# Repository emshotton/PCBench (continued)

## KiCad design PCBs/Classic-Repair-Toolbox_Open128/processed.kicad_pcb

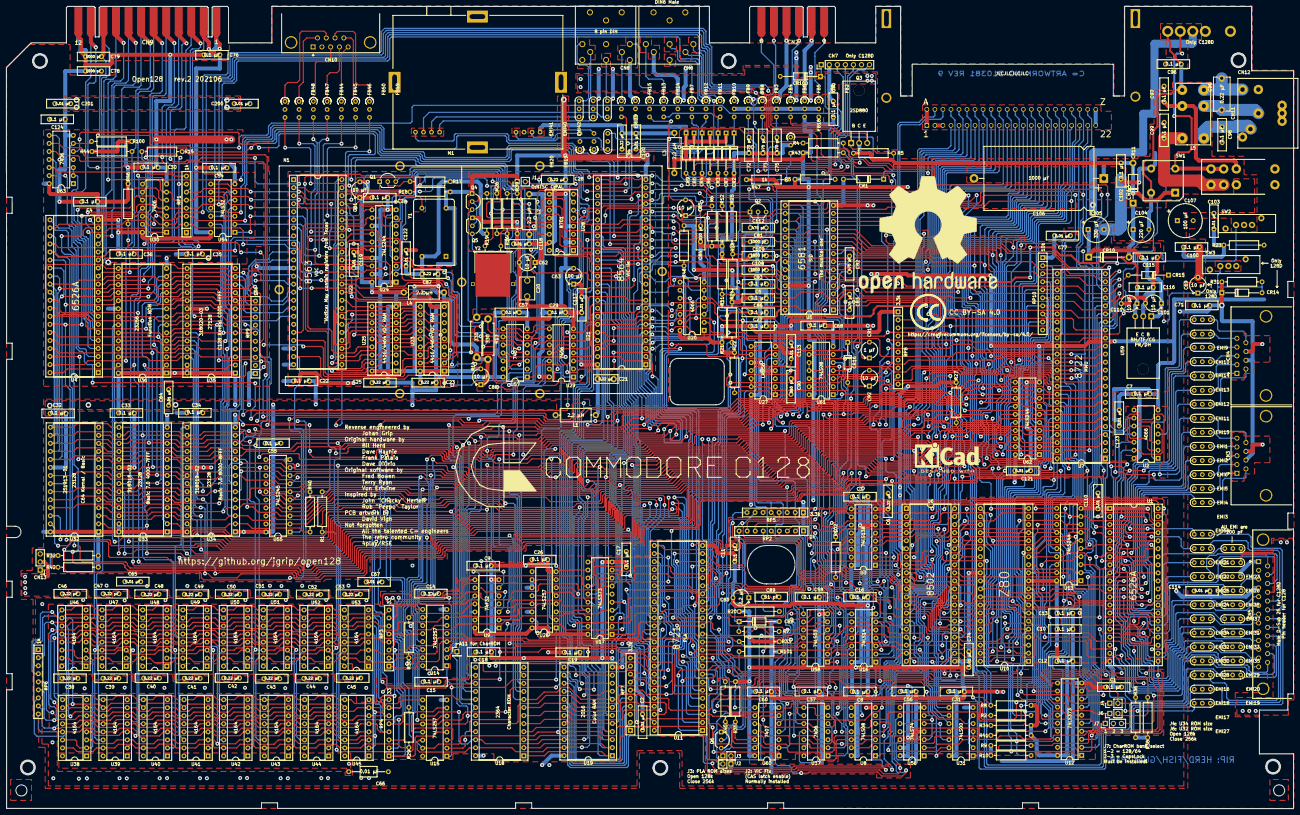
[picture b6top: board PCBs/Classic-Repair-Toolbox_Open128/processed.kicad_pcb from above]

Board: 2 copper layers, 406.6 x 253.4 mm, 371 parts (1 on the bottom side), 400 nets.

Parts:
C1, C3, C4, C5, C7, C8, C9, C10, C11, C12, C13, C14, C15, C16, C17, C18, C19, C22, C24, C26, C27, C29, C30, C31, C32, C33, C34, C35, C36, C37, C54, C55, C56, C57, C58, C60, C68, C70, C71, C76, C86, C93, C96, C97, C98, C99, C100, C102, C115, C116, C124: 0.1 µF; C_Disc_D10.0mm_W2.5mm_P5.00mm
C2, C64, C65, C67, C74, C77, C103, C110, C113, C114, C117, C118, C119, C120, C121, C122, C123, C200, C201: 0.01 µF; C_Disc_D10.0mm_W2.5mm_P5.00mm
C6, C23, C25, C28, C38, C39, C40, C41, C42, C43, C44, C45, C46, C47, C48, C49, C50, C51, C52, C53, C87, C94: 0.22 µF; C_Disc_D10.0mm_W2.5mm_P5.00mm
C20: 40 pF; C_Adjustable_L7.0mm_W4.5mm_P5.00mm
C21: 0.22 µF; C_Disc_D7.5mm_W2.5mm_P5.00mm
C61, C62, C69, C85, C88, C92, C101, C111: 10 µF; CP_Radial_Tantal_D5.0mm_P5.00mm
C63: 100 µF; CP_Radial_Tantal_D5.0mm_P5.00mm
C66: 0.01 µF; C_Axial_L5.1mm_D3.1mm_P12.50mm_Horizontal
C72, C73, C75, C82, C83, C112: 470 pF; C_Disc_D10.0mm_W2.5mm_P5.00mm
C78, C79, C81: 1000 pF; C_Disc_D10.0mm_W2.5mm_P5.00mm
C80: 2.2 µF; CP_Radial_Tantal_D5.0mm_P5.00mm
C84: 220 pF; C_Disc_D10.0mm_W2.5mm_P5.00mm
C89: 51 pF; C_Disc_D10.0mm_W2.5mm_P5.00mm
C90: 360 pF; C_Disc_D10.0mm_W2.5mm_P5.00mm
C91: 1 µF; CP_Radial_Tantal_D5.0mm_P5.00mm
C95: 0.22 µF; C_Disc_D10.5mm_W5.0mm_P10.00mm
C104: 220 µF; CP_Radial_Tantal_D8.0mm_P5.00mm
C105: 330 µF; CP_Radial_Tantal_D8.0mm_P5.00mm
C106: 1000 µF; CP_Axial_L34.5mm_D20.0mm_P41.00mm_Horizontal
C107: 100 µF; CP_Radial_Tantal_D10.5mm_P5.00mm
C108, C109: 1800 pF; C_Disc_D10.0mm_W2.5mm_P5.00mm
CN1: Expansion bus; EXPANSIONPORT
CN2: Cassette; CASSETTEPORT
CN3: Port1 Male DB9; DSUB-9_Male_Horizontal_P2.77x2.84mm_EdgePinOffset14.56mm_Ho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
CN4: Port2 Male DB9; DSUB-9_Male_Horizontal_P2.77x2.84mm_EdgePinOffset14.56mm_Ho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
CN5: Conn_01x25; DSUB-25_Female_Horizontal_P2.77x2.84mm_EdgePinOffset7.70mm_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
CN6: DIN6 Male; Connector_DIN_Female_6Pin_3rows
CN7: 7 pin post; PinHeader_1x07_P2.54mm_Vertical
CN8: 8 pin DIN; Connector_DIN_Female_8Pin_3rows
CN9: User Port; USERPORT
CN10: RGBI 9-pin DIN; DSUB-9_Male_Horizontal_P2.77x2.84mm_EdgePinOffset7.70mm_Hou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
CN11: Power DIN connector; Connector_Power_5pin_252167_01
CN12: 6 pin post; CN12_C128D_power
CN13: Power LED; PinHeader_1x03_P2.54mm_Vertical
CN20: TA11; PinHeader_1x01_P2.54mm_Vertical
CR1: 6.8v; D_DO-35_SOD27_P12.70mm_Horizontal
CR2, CR3, CR4, CR5, CR6, CR7, CR9, CR14, CR15, CR16, CR100: 1N914; D_DO-35_SOD27_P12.70mm_Horizontal
CR8: 1N4371; D_DO-35_SOD27_P12.70mm_Horizontal
CR10, CR11: 1N4001; D_DO-41_SOD81_P12.70mm_Horizontal
CR13: 251026-01; BRIDGE_RECTIFIER
EMI1, EMI2, EMI9, EMI10, EMI11: 47 pF; EMI-Filter
EMI3, EMI4, EMI5, EMI6, EMI12, EMI13, EMI14, EMI15, EMI16, EMI17, EMI18, EMI19, EMI20, EMI21, EMI22, EMI23, EMI24, EMI25, EMI26, EMI27, EMI28, EMI29, EMI30, EMI31, EMI32, EMI33, EMI34, EMI35, EMI37, EMI38, EMI40, EMI41, EMI42, EMI69: 100 pF; EMI-Filter
EMI39: 270 pF; EMI-Filter
FB1, FB2, FB3, FB4, FB5, FB6, FB7, FB8, FB9, FB10, FB11, FB12, FB13, FB14, FB15, FB18, FB19, FB20, FB44, FB45, FB46, FB47, FB48, FB49, FB50: Ferrite_Bead_Small; Ferrite_Bead_vertical
J1: C:PAL / O:NTSC; PinHeader_1x02_P2.54mm_Vertical
J2, J3: Close to enable CAS latch; PinHeader_1x02_P2.54mm_Vertical
J4, J6: 128/256k; PinHeader_1x02_P2.54mm_Vertical
J7: SolderJumper_3_Bridged12; PinHeader_1x03_P2.54mm_Vertical
L1, L2, L3, L4: 2.2 µH; L_Axial_L9.5mm_D4.0mm_P12.70mm_Horizontal_Fastron_SMCC
L5: 251878-01; Noise_Filter_Power_251878_01
LOGO1: OSHW logo; OSHW-Logo2_48.7x40mm_SilkScreen
LOGO2: KiCad logo; KiCad-Logo2_8mm_SilkScreen
LOGO3: C128 logo; C128-logo
LOGO4: Creative Commons; Symbol_CreativeCommons_SilkScreenTop_Type2_Big
M1: RF_Modulator; RF_modulator
N1: RF Cage; RF_Cage
Q1, Q2, Q4, Q5, Q6: 2SC1815; TO-92_Inline_Wide
Q3: 2SD880; TO-220-3_Horizontal_TabDown
R1, R29, R30, R40, R102: 68; R_Axial_DIN0309_L9.0mm_D2.5mm_P12.70mm_Horizontal
R2, R4, R15, R26, R35: 100; R_Axial_DIN0309_L9.0mm_D2.5mm_P12.70mm_Horizontal
R3, R11, R12, R47, R100, R101: 1k; R_Axial_DIN0309_L9.0mm_D2.5mm_P12.70mm_Horizontal
R5: 470; R_Axial_DIN0309_L9.0mm_D2.5mm_P12.70mm_Horizontal
R6, R22, R24: 47k; R_Axial_DIN0309_L9.0mm_D2.5mm_P12.70mm_Horizontal
R7: 560; R_Axial_DIN0309_L9.0mm_D2.5mm_P12.70mm_Horizontal
R8, R10, R43, R44, R46: 3.3k; R_Axial_DIN0309_L9.0mm_D2.5mm_P12.70mm_Horizontal
R9, R20, R28, R33, R34, R36, R38, R48: 10k; R_Axial_DIN0309_L9.0mm_D2.5mm_P12.70mm_Horizontal
R13, R14: 330; R_Axial_DIN0411_L9.9mm_D3.6mm_P12.70mm_Horizontal
R16, R39: 120; R_Axial_DIN0309_L9.0mm_D2.5mm_P12.70mm_Horizontal
R17: 47; R_Axial_DIN0309_L9.0mm_D2.5mm_P12.70mm_Horizontal
R18: 82; R_Axial_DIN0309_L9.0mm_D2.5mm_P12.70mm_Horizontal
R19: 330; R_Axial_DIN0309_L9.0mm_D2.5mm_P12.70mm_Horizontal
R21: 470k; R_Axial_DIN0309_L9.0mm_D2.5mm_P12.70mm_Horizontal
R23, R25, R31: 100k; R_Axial_DIN0309_L9.0mm_D2.5mm_P12.70mm_Horizontal
R27: 4.7k; R_Axial_DIN0309_L9.0mm_D2.5mm_P12.70mm_Horizontal
R32, R42: 180; R_Axial_DIN0309_L9.0mm_D2.5mm_P12.70mm_Horizontal
R41: 680; R_Axial_DIN0309_L9.0mm_D2.5mm_P12.70mm_Horizontal
R45: 1.2k; R_Axial_DIN0309_L9.0mm_D2.5mm_P12.70mm_Horizontal
RP1: 1k; R_Array_SIP8
RP2, RP6: 1k; R_Array_SIP9
RP3, RP4: 33; R_Array_SIP8
RP5: 3.3k; R_Array_SIP8
RP7, RP8: 3.3k; R_Array_SIP10
RP9, RP10: 10k; R_Array_SIP10
SW1: Power switch; Power_Switch
SW2: Reset Switch; Switch-Pushbutton
SW3: Disk Reset; Switch-Pushbutton
U1, U4: 6526A; DIP-40_W15.24mm_Socket
U2, U20: 4066; DIP-14_W7.62mm
U3: 74LS138; DIP-16_W7.62mm
U5: 6581; DIP-28_W15.24mm_Socket
U6: 8502; DIP-40_W15.24mm_Socket
U7: 8722; DIP-48_W15.24mm_Socket
U8, U61: 74LS08; DIP-14_W7.62mm
U9: 74F32; DIP-14_W7.62mm
U10: Z80; DIP-40_W15.24mm_Socket
U11: 8721; DIP-48_W15.24mm_Socket
U12, U17: 74LS373; DIP-20_W7.62mm
U13, U24, U62: 74LS244; DIP-20_W7.62mm
U14, U15, U26: 74LS257; DIP-16_W7.62mm
U16: 74LS14; DIP-14_W7.62mm
U18: 2364; DIP-24_W15.24mm_Socket
U19: 2016; DIP-24_W15.24mm_Socket
U21: 8564; DIP-48_W15.24mm_Socket
U22: 8563; DIP-48_W15.24mm_Socket
U23, U25: 4464; DIP-18_W7.62mm_Socket
U27: LM556; DIP-14_W7.62mm
U28: 8701; DIP-16_W7.62mm_Socket
U29, U30, U37, U63: 7406; DIP-14_W7.62mm
U31: 74LS00; DIP-14_W7.62mm
U32, U33, U34: 23128; DIP-28_W15.24mm_Socket
U35: 318020-03; DIP-28_W15.24mm_Socket
U36: 23256; DIP-28_W15.24mm_Socket
U38, U39, U40, U41, U42, U43, U44, U45, U46, U47, U48, U49, U50, U51, U52, U53: 4164; DIP-16_W7.62mm_Socket
U54: 74LS32; DIP-14_W7.62mm
U55: 74LS245; DIP-20_W7.62mm
U56: 74LS74; DIP-14_W7.62mm
U57, U60: 7407; DIP-14_W7.62mm
U58: 74LS03; DIP-14_W7.62mm
U59: L7812; TO-220-3_Horizontal_TabDown
Y1: 16 MHz; Oscillator_DIP-14
Y2: 17.73447 MHz (PAL) / 14.31818 MHz (NTSC); Crystal_HC49-U_Horizontal_1EP_style2

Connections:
1MHZ: CN1.E, R102.2, U4.25, U5.6, U21.18
2MHZ: U6.1, U7.33, U21.23, U22.4
9VAC1: C79.2, CN9.10, CN12.5, CR13.2, R7.1, SW1.4
9VAC2: C78.2, C96.1, C104.2, CN9.11, CN12.6, CR13.4, L5.6
40_80: EMI16.3, RP8.9, U7.48
128_64: J6.1, J7.1, U7.47, U8.9, U11.15
+5V: C1.2, C2.1, C3.2, C4.2, C5.2, C6.2, C7.1, C8.2, C9.2, C10.2, C11.2, C12.2, C13.2, C14.2, C15.2, C16.2, C17.2, C18.2, C19.2, C22.2, C23.2, C24.2, C25.2, C26.2, C27.1, C29.2, C30.2, C31.2, C32.2, C33.2, C34.2, C35.2, C36.2, C37.2, C38.1, C39.1, C40.1, C41.1, C42.1, C43.1, C44.1, C45.1, C46.1, C47.1, C48.1, C49.1, C50.1, C51.1, C52.1, C53.1, C54.2, C55.2, C56.2, C57.2, C58.2, C60.2, C61.1, C64.1, C65.1, C66.1, C67.1, C68.2, C70.2, C71.1, C74.2, C76.2, C77.2, C100.1, C103.1, C107.1, C110.2, C114.1, C119.2, C121.2, C123.2, C124.2, CN1.2, CN1.3, CN3.7, CN4.7, CN5.4, CN9.2, CN12.4, CR5.1, CR6.1, CR7.1, CR9.1, CR14.1, CR15.1, FB1.2, FB13.2, L1.2, L2.1, L3.1, L4.1, R3.1, R8.2, R9.1, R10.1, R20.1, R21.1, R22.1, R23.1, R24.1, R27.1, R31.1, R32.2, R33.1, R34.2, R35.2, R36.2, R38.1, R40.1, R41.2, R42.2, R43.1, R44.1, R46.1, R47.1, R48.2, R100.1, RP1.1, RP2.1, RP5.1, RP6.1, RP7.1, RP8.1, RP9.1, RP10.1, SW1.2, U1.20, U2.14, U3.6, U3.16, U4.20, U5.25, U6.6, U7.1, U8.14, U9.14, U10.11, U11.8, U11.48, U12.20, U13.20, U14.16, U15.16, U16.14, U17.20, U18.24, U19.24, U20.14, U22.37, U23.9, U24.20, U25.9, U26.16, U27.4, U27.10, U27.14, U29.14, U30.14, U31.14, U32.1, U32.28, U33.1, U33.27, U33.28, U34.1, U34.28, U35.1, U35.27, U35.28, U36.1, U36.28, U37.14, U38.8, U39.8, U40.8, U41.8, U42.8, U43.8, U44.8, U45.8, U46.8, U47.8, U48.8, U49.8, U50.8, U51.8, U52.8, U53.8, U54.14, U55.20, U56.1, U56.4, U56.13, U56.14, U57.14, U58.14, U60.14, U61.14, U62.20, U63.14
+9V: C102.1, C106.1, CR11.2, CR13.1, Q3.2, R5.2
+12V: C86.2, C111.1, C116.1, Q2.2, R45.2, U5.28, U59.3
/Address Multiplexing/A0: RP9.10, U1.38, U4.38, U5.9, U6.7, U7.18, U10.30, U15.13, U22.8, U32.10, U33.10, U34.10, U35.10, U36.10, U55.3
/Address Multiplexing/A1: RP9.9, U1.37, U4.37, U5.10, U6.8, U7.19, U10.31, U15.10, U32.9, U33.9, U34.9, U35.9, U36.9, U55.5
/Address Multiplexing/A2: RP9.8, U1.36, U4.36, U5.11, U6.9, U7.20, U10.32, U15.6, U32.8, U33.8, U34.8, U35.8, U36.8, U55.7
/Address Multiplexing/A3: RP9.7, U1.35, U4.35, U5.12, U6.10, U7.21, U10.33, U15.3, U32.7, U33.7, U34.7, U35.7, U36.7, U55.9
/Address Multiplexing/A4: RP9.6, U5.13, U6.11, U10.34, U14.13, U32.6, U33.6, U34.6, U35.6, U36.6, U54.13, U55.8
/Address Multiplexing/A5: RP9.5, U6.12, U10.35, U14.10, U32.5, U33.5, U34.5, U35.5, U36.5, U54.12, U55.6
/Address Multiplexing/A6: RP9.4, U6.13, U10.36, U14.6, U32.4, U33.4, U34.4, U35.4, U36.4, U54.5, U55.4
/Address Multiplexing/A7: RP9.3, U6.14, U10.37, U14.3, U32.3, U33.3, U34.3, U35.3, U36.3, U54.4, U55.2
/Address Multiplexing/A8: RP10.2, U3.1, U6.15, U7.24, U10.38, U32.25, U33.25, U34.25, U35.25, U36.25, U62.9
/Address Multiplexing/A9: RP10.3, U3.2, U6.16, U7.25, U10.39, U32.24, U33.24, U34.24, U35.24, U36.24, U62.12
/Address Multiplexing/A10: RP10.4, U6.17, U7.26, U10.40, U11.6, U31.9, U32.21, U33.21, U34.21, U35.21, U36.21, U62.7
/Address Multiplexing/A11: RP10.5, U3.3, U6.18, U7.27, U10.1, U11.5, U32.23, U33.23, U34.23, U35.23, U36.23, U62.14
/Address Multiplexing/A12: RP10.6, U6.19, U7.28, U10.2, U11.4, U33.2, U34.2, U36.2, U62.5
/Address Multiplexing/A13: RP10.7, U6.20, U7.29, U8.12, U10.3, U11.3, U33.26, U34.26, U35.26, U36.26, U62.16
/Address Multiplexing/A14: RP10.8, U6.22, U7.30, U10.4, U11.2, U36.27, U62.3
/Address Multiplexing/A15: J4.1, RP10.9, U6.23, U7.31, U10.5, U11.1, U62.18
/Address Multiplexing/MA0: RP4.4, RP6.8, U38.5, U39.5, U40.5, U41.5, U42.5, U43.5, U44.5, U45.5, U46.5, U47.5, U48.5, U49.5, U50.5, U51.5, U52.5, U53.5
/Address Multiplexing/MA1: RP4.8, RP6.2, U38.7, U39.7, U40.7, U41.7, U42.7, U43.7, U44.7, U45.7, U46.7, U47.7, U48.7, U49.7, U50.7, U51.7, U52.7, U53.7
/Address Multiplexing/MA2: RP4.6, RP6.6, U38.6, U39.6, U40.6, U41.6, U42.6, U43.6, U44.6, U45.6, U46.6, U47.6, U48.6, U49.6, U50.6, U51.6, U52.6, U53.6
/Address Multiplexing/MA3: RP4.2, RP6.7, U38.12, U39.12, U40.12, U41.12, U42.12, U43.12, U44.12, U45.12, U46.12, U47.12, U48.12, U49.12, U50.12, U51.12, U52.12, U53.12
/Address Multiplexing/MA4: RP3.6, RP6.5, U38.11, U39.11, U40.11, U41.11, U42.11, U43.11, U44.11, U45.11, U46.11, U47.11, U48.11, U49.11, U50.11, U51.11, U52.11, U53.11
/Address Multiplexing/MA5: RP3.8, RP6.4, U38.10, U39.10, U40.10, U41.10, U42.10, U43.10, U44.10, U45.10, U46.10, U47.10, U48.10, U49.10, U50.10, U51.10, U52.10, U53.10
/Address Multiplexing/MA6: RP3.4, RP6.9, U38.13, U39.13, U40.13, U41.13, U42.13, U43.13, U44.13, U45.13, U46.13, U47.13, U48.13, U49.13, U50.13, U51.13, U52.13, U53.13
/Address Multiplexing/MA7: RP3.2, RP6.3, U38.9, U39.9, U40.9, U41.9, U42.9, U43.9, U44.9, U45.9, U46.9, U47.9, U48.9, U49.9, U50.9, U51.9, U52.9, U53.9
/Address Multiplexing/SA0: CN1.Y, U17.2, U18.8, U19.8, U55.17
/Address Multiplexing/SA1: CN1.X, U17.5, U18.7, U19.7, U55.15
/Address Multiplexing/SA2: CN1.W, U17.6, U18.6, U19.6, U55.13
/Address Multiplexing/SA3: CN1.V, U17.9, U18.5, U19.5, U55.11
/Address Multiplexing/SA4: CN1.U, U17.12, U18.4, U19.4, U55.12
/Address Multiplexing/SA5: CN1.T, U17.15, U18.3, U19.3, U55.14
/Address Multiplexing/SA6: CN1.S, U17.16, U18.2, U19.2, U55.16
/Address Multiplexing/SA7: CN1.R, U17.19, U18.1, U19.1, U55.18
/Address Multiplexing/TA8: CN1.P, U7.10, U15.14, U18.23, U19.23, U21.40, U62.11
/Address Multiplexing/TA9: CN1.N, U7.9, U15.11, U18.22, U19.22, U21.41, U62.8
/Address Multiplexing/TA10: CN1.M, U7.8, U15.5, U18.19, U21.42, U62.13
/Address Multiplexing/TA11: CN1.L, CN20.1, U7.7, U15.2, U18.18, U21.31, U62.6
/Address Multiplexing/TA12: CN1.K, RP8.5, U7.6, U14.14, U32.2, U35.2, U62.15
/Address Multiplexing/TA13: CN1.J, RP8.4, U7.5, U14.11, U62.4
/Address Multiplexing/TA14: CN1.H, RP8.3, U7.4, U8.13, U14.5, U62.17
/Address Multiplexing/TA15: CN1.F, RP8.2, U7.3, U14.2, U62.2
/Address Multiplexing/VMA0: RP4.3, U15.12, U17.3, U21.32
/Address Multiplexing/VMA1: RP4.7, U15.9, U17.4, U21.33
/Address Multiplexing/VMA2: RP4.5, U15.7, U17.7, U21.34
/Address Multiplexing/VMA3: RP4.1, U15.4, U17.8, U21.35
/Address Multiplexing/VMA4: RP3.5, U11.19, U14.12, U17.13, U21.36
/Address Multiplexing/VMA5: RP3.7, U11.20, U14.9, U17.14, U21.37
/Address Multiplexing/VMA6: RP3.3, U14.7, U26.4
/Address Multiplexing/VMA7: RP3.1, U14.4, U26.7
/CPU 8502/D0: CN1.21, U1.33, U4.33, U5.15, U6.38, U7.35, U12.3, U13.3, U18.9, U20.2, U21.7, U22.18, U32.11, U33.11, U34.11, U35.11, U36.11, U38.2, U38.14, U46.2, U46.14
/CPU 8502/D1: CN1.20, U1.32, U4.32, U5.16, U6.37, U7.36, U12.4, U13.5, U18.10, U20.3, U21.6, U22.17, U32.12, U33.12, U34.12, U35.12, U36.12, U39.2, U39.14, U47.2, U47.14
/CPU 8502/D2: CN1.19, U1.31, U4.31, U5.17, U6.36, U7.37, U12.7, U13.7, U18.11, U20.9, U21.5, U22.16, U32.13, U33.13, U34.13, U35.13, U36.13, U40.2, U40.14, U48.2, U48.14
/CPU 8502/D3: CN1.18, U1.30, U4.30, U5.18, U6.35, U7.38, U12.8, U13.9, U18.13, U20.10, U21.4, U22.15, U32.15, U33.15, U34.15, U35.15, U36.15, U41.2, U41.14, U49.2, U49.14
/CPU 8502/D4: CN1.17, U1.29, U4.29, U5.19, U6.34, U7.39, U12.13, U13.12, U18.14, U21.3, U22.14, U32.16, U33.16, U34.16, U35.16, U36.16, U42.2, U42.14, U50.2, U50.14
/CPU 8502/D5: CN1.16, U1.28, U4.28, U5.20, U6.33, U7.40, U12.14, U13.14, U18.15, U21.2, U22.13, U32.17, U33.17, U34.17, U35.17, U36.17, U43.2, U43.14, U51.2, U51.14
/CPU 8502/D6: CN1.15, U1.27, U4.27, U5.21, U6.32, U7.41, U12.17, U13.16, U18.16, U21.1, U22.11, U32.18, U33.18, U34.18, U35.18, U36.18, U44.2, U44.14, U52.2, U52.14
/CPU 8502/D7: CN1.14, U1.26, U4.26, U5.22, U6.31, U7.42, U12.18, U13.18, U18.17, U21.47, U22.10, U32.19, U33.19, U34.19, U35.19, U36.19, U45.2, U45.14, U53.2, U53.14
/CPU 8502/P0: RP7.6, U6.30, U11.22
/CPU 8502/P1: RP7.7, U6.29, U11.23
/CPU 8502/P2: RP7.8, U6.28, U11.25
/CPU 8502/P3: R4.2, U6.27
/CPU 8502/P4: C72.2, FB3.2, RP5.2, U6.26
/CPU 8502/P5: U6.25, U30.13
/CPU Z80/ZD0: U10.14, U12.2, U13.17
/CPU Z80/ZD1: U10.15, U12.5, U13.15
/CPU Z80/ZD2: U10.12, U12.6, U13.13
/CPU Z80/ZD3: U10.8, U12.9, U13.11
/CPU Z80/ZD4: U10.7, U12.12, U13.8
/CPU Z80/ZD5: U10.9, U12.15, U13.6
/CPU Z80/ZD6: U10.10, U12.16, U13.4
/CPU Z80/ZD7: U10.13, U12.19, U13.2
/I/O/COL0: EMI11.3, EMI20.3, U1.2
/I/O/COL1: EMI12.3, EMI21.3, U1.3
/I/O/COL2: EMI13.3, EMI22.3, U1.4
/I/O/COL3: EMI14.3, EMI23.3, U1.5
/I/O/COL4: EMI15.3, EMI24.3, U1.6
/I/O/COL5: EMI25.3, U1.7
/I/O/COL6: EMI26.3, U1.8, U2.6, U2.12
/I/O/COL7: EMI27.3, U1.9, U2.5, U2.13
/I/O/Casette Interface/CASS3: FB5.2, Q3.3
/I/O/Casette Interface/CASS5: C73.2, FB4.2, R4.1
/I/O/Casette Interface/CCN1: CN2.1, CN2.A, FB2.1
/I/O/Casette Interface/CCN2: CN2.2, CN2.B, FB1.1
/I/O/Casette Interface/CCN3: CN2.3, CN2.C, FB5.1
/I/O/Casette Interface/CCN4: CN2.4, CN2.D, FB6.1
/I/O/Casette Interface/CCN5: CN2.5, CN2.E, FB4.1
/I/O/Casette Interface/CCN6: CN2.6, CN2.F, FB3.1
/I/O/Casette Interface/READ: C75.2, FB6.2, R2.1, RP5.4, U60.4
/I/O/Control Ports/Control Ports-EMI/IN_FBTNA: CN3.6, EMI69.1
/I/O/Control Ports/Control Ports-EMI/IN_FBTNB: CN4.6, EMI15.1
/I/O/Control Ports/Control Ports-EMI/IN_JOYA0: CN3.1, EMI3.1
/I/O/Control Ports/Control Ports-EMI/IN_JOYA1: CN3.2, EMI4.1
/I/O/Control Ports/Control Ports-EMI/IN_JOYA2: CN3.3, EMI5.1
/I/O/Control Ports/Control Ports-EMI/IN_JOYA3: CN3.4, EMI6.1
/I/O/Control Ports/Control Ports-EMI/IN_JOYB0: CN4.1, EMI11.1
/I/O/Control Ports/Control Ports-EMI/IN_JOYB1: CN4.2, EMI12.1
/I/O/Control Ports/Control Ports-EMI/IN_JOYB2: CN4.3, EMI13.1
/I/O/Control Ports/Control Ports-EMI/IN_JOYB3: CN4.4, EMI14.1
/I/O/Control Ports/Control Ports-EMI/IN_POTAX: CN3.9, EMI1.1
/I/O/Control Ports/Control Ports-EMI/IN_POTAY: CN3.5, EMI2.1
/I/O/Control Ports/Control Ports-EMI/IN_POTBX: CN4.9, EMI9.1
/I/O/Control Ports/Control Ports-EMI/IN_POTBY: CN4.5, EMI10.1
/I/O/Control Ports/Control Ports-EMI/OUT_POTAX: EMI1.3, U2.8
/I/O/Control Ports/Control Ports-EMI/OUT_POTAY: EMI2.3, U2.11
/I/O/Control Ports/Control Ports-EMI/OUT_POTBX: EMI9.3, U2.1
/I/O/Control Ports/Control Ports-EMI/OUT_POTBY: EMI10.3, U2.4
/I/O/Keyboard/Key-EMI/IN_4080: CN5.24, EMI16.1
/I/O/Keyboard/Key-EMI/IN_COL0: CN5.13, EMI20.1
/I/O/Keyboard/Key-EMI/IN_COL1: CN5.19, EMI21.1
/I/O/Keyboard/Key-EMI/IN_COL2: CN5.18, EMI22.1
/I/O/Keyboard/Key-EMI/IN_COL3: CN5.17, EMI23.1
/I/O/Keyboard/Key-EMI/IN_COL4: CN5.16, EMI24.1
/I/O/Keyboard/Key-EMI/IN_COL5: CN5.15, EMI25.1
/I/O/Keyboard/Key-EMI/IN_COL6: CN5.14, EMI26.1
/I/O/Keyboard/Key-EMI/IN_COL7: CN5.20, EMI27.1
/I/O/Keyboard/Key-EMI/IN_GND: CN5.1, EMI38.1
/I/O/Keyboard/Key-EMI/IN_K0: CN5.21, EMI17.1
/I/O/Keyboard/Key-EMI/IN_K1: CN5.22, EMI18.1
/I/O/Keyboard/Key-EMI/IN_K2: CN5.23, EMI19.1
/I/O/Keyboard/Key-EMI/IN_ROW0: CN5.12, EMI28.1
/I/O/Keyboard/Key-EMI/IN_ROW1: CN5.11, EMI29.1
/I/O/Keyboard/Key-EMI/IN_ROW2: CN5.10, EMI30.1
/I/O/Keyboard/Key-EMI/IN_ROW3: CN5.5, EMI31.1
/I/O/Keyboard/Key-EMI/IN_ROW4: CN5.8, EMI32.1
/I/O/Keyboard/Key-EMI/IN_ROW5: CN5.7, EMI33.1
/I/O/Keyboard/Key-EMI/IN_ROW6: CN5.6, EMI34.1
/I/O/Keyboard/Key-EMI/IN_ROW7: CN5.9, EMI35.1
/I/O/Keyboard/Key-EMI/IN_RSTR: CN5.3, EMI37.1
/I/O/Keyboard/RESTORE: EMI37.3, R9.2, U16.9
/I/O/PB0: CN9.C, U4.10
/I/O/PB1: CN9.D, U4.11
/I/O/PB2: CN9.E, U4.12
/I/O/PB3: CN9.F, U4.13
/I/O/PB4: CN9.H, U4.14
/I/O/PB5: CN9.J, U4.15
/I/O/PB6: CN9.K, U4.16
/I/O/PB7: CN9.L, U4.17
/I/O/ROW0: EMI3.3, EMI28.3, U1.10
/I/O/ROW1: EMI4.3, EMI29.3, U1.11
/I/O/ROW2: EMI5.3, EMI30.3, U1.12
/I/O/ROW3: EMI6.3, EMI31.3, U1.13
/I/O/ROW5: EMI33.3, U1.15
/I/O/ROW6: EMI34.3, U1.16
/I/O/ROW7: EMI35.3, U1.17
/I/O/Serial Bus/ATN: CN7.3, CN9.9, CR4.1, CR5.2, FB10.2, RP1.5, U30.6
/I/O/Serial Bus/ATNOUT: U4.5, U30.5
/I/O/Serial Bus/CLK: CN7.4, CR3.1, CR6.2, FB9.2, RP1.4, U4.8, U30.4
/I/O/Serial Bus/CLKOUT: U4.6, U30.3
/I/O/Serial Bus/CNT: CN9.4, RP5.5, U1.40, U37.13, U58.3
/I/O/Serial Bus/DATA: CN7.5, CR2.1, CR7.2, FB8.2, RP1.3, U4.9, U16.1, U30.2, U60.8
/I/O/Serial Bus/DATAOUT: U4.7, U30.1
/I/O/Serial Bus/SP: CN9.5, RP5.6, U1.39, U37.3, U58.8
/I/O/Serial Bus/~EXTRES: CN9.3, FB11.2, RP1.6, U57.10
/I/O/Serial Bus/~SRQIN: CN7.1, CR9.2, CR100.1, FB7.2, R3.2, U16.3, U60.3, U60.6
/I/O/Userport/CNT2: CN9.6, RP5.3, U4.40
/I/O/Userport/PA2: CN9.M, U4.4
/I/O/Userport/SP2: CN9.7, R44.2, U4.39
/I/O/Userport/~FLAG2: CN9.B, R46.2, U4.24
/I/O/Userport/~PC2: CN9.8, U4.18
/Memory Management/IOSEL: U7.13, U11.16
/Memory Management/ROMBANKHI: U7.14, U11.17
/Memory Management/ROMBANKLO: U7.15, U11.18
/Memory Management/~IO_CS: U3.5, U11.38
/VDC/B: FB46.2, U24.14, U54.9
/VDC/DA0: U22.26, U23.14, U25.14
/VDC/DA1: U22.27, U23.13, U25.13
/VDC/DA2: U22.28, U23.12, U25.12
/VDC/DA3: U22.29, U23.11, U25.11
/VDC/DA4: U22.30, U23.8, U25.8
/VDC/DA5: U22.31, U23.7, U25.7
/VDC/DA6: U22.32, U23.6, U25.6
/VDC/DA7: U22.33, U23.10, U25.10
/VDC/DD0: U22.34, U23.2
/VDC/DD1: U22.35, U23.3
/VDC/DD2: U22.36, U23.15
/VDC/DD3: U22.38, U23.17
/VDC/DD4: U22.39, U25.2
/VDC/DD5: U22.40, U25.3
/VDC/DD6: U22.41, U25.15
/VDC/DD7: U22.42, U25.17
/VDC/G: FB45.2, U24.16, U54.2
/VDC/HSYNC: FB49.2, U24.5, U29.9, U57.9
/VDC/I: FB47.2, U24.12, U57.3
/VDC/MONOCHROME: FB48.2, Q1.1, R18.1
/VDC/R: FB44.2, U24.18, U54.1
/VDC/VSYNC: FB50.2, U24.9, U29.5, U57.5
/VIC/CD0: U19.9, U20.1, U21.46
/VIC/CD1: U19.10, U20.4, U21.45
/VIC/CD2: U19.11, U20.8, U21.44
/VIC/CD3: U19.13, U20.11, U21.43
/VIC/RF Modulator and AV connectors/CHROMA: FB20.1, U21.16
/VIC/RF Modulator and AV connectors/SYNC_LUM: FB19.1, U21.17
AEC: U11.9, U17.1, U20.5, U20.6, U20.12, U20.13, U21.12, U26.15, U29.11, U61.2
AUDIO_OUT: C85.2, EMI39.1, FB14.2, R6.1
BA: CN1.12, U11.21, U21.10, U60.1, U61.4, U63.5
CAPSLK: CN5.25, J7.3, RP8.10, U6.24
CLRBNK: U11.32, U19.19
D1MHZ: R102.1, U1.25, U12.11, U56.3, U56.10
EXT_AUDIO: C93.1, U5.26
F_R~W: U8.6, U22.9, U57.1
GAEC: U7.16, U31.13, U61.3
GND: C1.1, C2.2, C3.1, C4.1, C5.1, C6.1, C7.2, C8.1, C9.1, C10.1, C11.1, C12.1, C13.1, C14.1, C15.1, C16.1, C17.1, C18.1, C19.1, C20.2, C21.2, C22.1, C23.1, C24.1, C25.1, C26.1, C27.2, C28.2, C29.1, C30.1, C31.1, C32.1, C33.1, C34.1, C35.1, C36.1, C37.1, C38.2, C39.2, C40.2, C41.2, C42.2, C43.2, C44.2, C45.2, C46.2, C47.2, C48.2, C49.2, C50.2, C51.2, C52.2, C53.2, C54.1, C55.1, C56.1, C57.1, C58.1, C60.1, C61.2, C62.2, C63.2, C64.2, C65.2, C66.2, C67.2, C68.1, C69.2, C70.1, C71.2, C72.1, C73.1, C74.1, C75.1, C76.1, C77.1, C78.1, C79.1, C80.2, C81.1, C84.1, C86.1, C87.2, C88.2, C90.1, C91.2, C92.2, C94.1, C96.2, C97.2, C98.2, C99.2, C100.2, C101.2, C102.2, C103.2, C105.2, C106.2, C107.2, C108.1, C109.1, C110.1, C111.2, C113.2, C114.2, C115.2, C116.2, C117.1, C118.2, C119.1, C120.2, C121.1, C122.2, C123.1, C124.1, C200.1, C200.2, C201.1, C201.2, CN1.1, CN1.22, CN1.A, CN1.Z, CN3.0, CN3.8, CN4.0, CN4.8, CN5.0, CN6.SH, CN7.2, CN8.2, CN8.SH, CN9.1, CN9.12, CN9.A, CN9.N, CN10.0, CN10.1, CN10.2, CN11.0, CN11.2, CN11.4, CN12.1, CN12.3, CN13.2, CR1.2, CR2.2, CR3.2, CR4.2, CR8.2, CR13.3, CR100.2, EMI1.2, EMI2.2, EMI3.2, EMI4.2, EMI5.2, EMI6.2, EMI9.2, EMI10.2, EMI11.2, EMI12.2, EMI13.2, EMI14.2, EMI15.2, EMI16.2, EMI17.2, EMI18.2, EMI19.2, EMI20.2, EMI21.2, EMI22.2, EMI23.2, EMI24.2, EMI25.2, EMI26.2, EMI27.2, EMI28.2, EMI29.2, EMI30.2, EMI31.2, EMI32.2, EMI33.2, EMI34.2, EMI35.2, EMI37.2, EMI38.2, EMI38.3, EMI39.2, EMI40.2, EMI41.2, EMI42.2, EMI69.2, FB1.3, FB2.2, FB2.3, FB3.3, FB4.3, FB5.3, FB6.3, FB7.3, FB8.3, FB9.3, FB10.3, FB11.3, FB12.2, FB12.3, FB13.3, FB14.3, FB15.3, FB18.3, FB19.3, FB20.3, FB44.3, FB45.3, FB46.3, FB47.3, FB48.3, FB49.3, FB50.3, J1.1, J2.1, J3.2, M1.3, N1.1, Q4.1, Q5.1, R6.2, R11.2, R12.2, R18.2, R25.1, R39.2, R101.1, SW1.0, SW2.0, SW2.2, SW3.0, SW3.2, U1.1, U2.7, U3.8, U4.1, U5.14, U6.21, U7.34, U8.7, U9.7, U10.29, U11.24, U12.10, U13.10, U14.8, U15.8, U16.7, U17.10, U18.12, U19.12, U20.7, U21.24, U22.12, U22.22, U22.24, U23.1, U23.18, U24.1, U24.10, U24.13, U24.17, U24.19, U25.1, U25.18, U26.8, U26.10, U26.11, U26.14, U27.7, U28.2, U28.4, U28.9, U29.7, U30.7, U31.7, U32.14, U32.20, U33.14, U33.20, U34.14, U34.20, U35.14, U35.20, U36.14, U36.20, U37.7, U38.16, U39.16, U40.16, U41.16, U42.16, U43.16, U44.16, U45.16, U46.16, U47.16, U48.16, U49.16, U50.16, U51.16, U52.16, U53.16, U54.7, U55.10, U56.7, U57.7, U58.7, U59.2, U60.7, U61.7, U62.10, U63.7, Y1.7, Y2.3
K0: EMI17.3, U21.26
K1: EMI18.3, U21.27
K2: EMI19.3, U21.28
MUX: U7.17, U14.1, U15.1, U21.21, U26.1, U29.13
unnamed: C20.1, U28.13, Y2.1
unnamed: C69.1, CR14.2, R15.1, R31.2, SW3.1, U16.11
unnamed: C80.1, CR8.1, R7.2, U16.5
unnamed: C82.1, U5.4
unnamed: C82.2, U5.3
unnamed: C83.1, U5.2
unnamed: C83.2, U5.1
unnamed: C89.1, R20.2, U37.2
unnamed: C89.2, R21.2, U27.6
unnamed: C90.2, R22.2, U27.1, U27.2
unnamed: C91.1, CR15.2, CR16.1, R23.2, SW2.1, U27.8
unnamed: C92.1, CR16.2, R24.2, U27.12, U27.13
unnamed: C93.2, FB15.2, R25.2
unnamed: C95.1, CN11.3, L5.5
unnamed: C95.2, CN11.5, L5.3
unnamed: C97.1, L5.4, SW1.3
unnamed: C98.1, CN11.1, L5.1
unnamed: C99.1, L5.2, SW1.1
unnamed: C101.1, C105.1, C115.1, CR10.1, U59.1
unnamed: C104.1, CR10.2, CR11.1
unnamed: C81.2, C112.1, Q2.3, R28.1
unnamed: C84.2, C85.1, C112.2, Q2.1, R12.1
unnamed: C113.1, U27.11
unnamed: C21.1, C63.1, C117.2, L1.1, U21.48
unnamed: C28.1, C62.1, C118.1, L2.2, U28.12, U28.15
unnamed: C94.2, C120.1, L3.2, M1.1
unnamed: C87.1, C88.1, C122.1, L4.2, R13.2, R14.2, R17.1, R19.1, Y1.14
unnamed: CN6.1, FB7.1
unnamed: CN6.2, FB12.1
unnamed: CN6.3, FB10.1
unnamed: CN6.4, FB9.1
unnamed: CN6.5, FB8.1
unnamed: CN6.6, FB11.1
unnamed: CN8.1, EMI41.3
unnamed: CN8.3, FB14.1
unnamed: CN8.4, EMI40.3
unnamed: CN8.5, FB15.1
unnamed: CN8.6, EMI42.3
unnamed: CN8.8, FB13.1
unnamed: CN10.3, FB44.1
unnamed: CN10.4, FB45.1
unnamed: CN10.5, FB46.1
unnamed: CN10.6, FB47.1
unnamed: CN10.7, FB48.1
unnamed: CN10.8, FB49.1
unnamed: CN10.9, FB50.1
unnamed: CN13.1, R32.1
unnamed: CN13.3, R42.1
unnamed: CR1.1, Q3.1, R5.1, U30.12
unnamed: EMI39.3, M1.8
unnamed: EMI40.1, M1.5
unnamed: EMI41.1, M1.6
unnamed: EMI42.1, M1.7
unnamed: FB18.2, R47.2, U29.2
unnamed: FB19.2, M1.2
unnamed: FB20.2, M1.4
unnamed: J1.2, U28.7
unnamed: J2.2, U11.7
unnamed: J3.1, R33.2, U11.27
unnamed: J4.2, R36.1, U34.27
unnamed: J6.2, R38.2, U32.27
unnamed: J7.2, U18.21
unnamed: Q1.2, R17.2
unnamed: Q1.3, Q4.2, Q5.2, R19.2, R26.1
unnamed: Q4.3, R13.1, U29.8, U57.6
unnamed: Q5.3, R14.1, U29.6, U57.8
unnamed: Q6.1, U10.6, U60.10
unnamed: Q6.2, R35.1
unnamed: Q6.3, R45.1, R101.2, U60.12
unnamed: R1.1, U38.4, U39.4, U40.4, U41.4, U42.4, U43.4, U44.4, U45.4, U46.4, U47.4, U48.4, U49.4, U50.4, U51.4, U52.4, U53.4
unnamed: R2.2, U1.24
unnamed: R8.1, U10.22, U31.1
unnamed: R11.1, R28.2, U5.27
unnamed: R15.2, U30.8
unnamed: R16.1, R26.2, U57.12
unnamed: R16.2, R39.1, U57.4
unnamed: R27.2, U6.39, U8.4
unnamed: R29.1, U38.15, U39.15, U40.15, U41.15, U42.15, U43.15, U44.15, U45.15
unnamed: R29.2, U9.8
unnamed: R30.1, U46.15, U47.15, U48.15, U49.15, U50.15, U51.15, U52.15, U53.15
unnamed: R30.2, U9.11
unnamed: R34.1, U10.17, U10.24
unnamed: R41.1, U29.12, U56.11
unnamed: R48.1, U21.11
unnamed: R100.2, U63.1, U63.4, U63.6
unnamed: RP2.2, U58.6, U60.5
unnamed: RP2.3, U37.12, U58.5
unnamed: RP2.4, U58.11, U60.9
unnamed: RP2.6, U37.4, U58.12
unnamed: RP7.2, U19.17
unnamed: RP7.3, U19.16
unnamed: RP7.4, U19.15
unnamed: RP7.5, U19.14
unnamed: RP7.9, U10.25, U37.6, U37.8, U60.2
unnamed: U3.4, U31.8
unnamed: U4.3, U63.13
unnamed: U6.2, U61.8
unnamed: U6.5, U61.10, U61.11
unnamed: U7.11, U9.5
unnamed: U7.12, U9.2
unnamed: U10.21, U12.1
unnamed: U9.1, U9.4, U11.41
unnamed: U16.2, U58.9
unnamed: U16.4, U58.2
unnamed: U16.8, U37.1
unnamed: U16.10, U30.11
unnamed: U8.10, U16.12
unnamed: U17.11, U26.12
unnamed: U19.21, U56.9
unnamed: U22.2, Y1.8
unnamed: U22.3, U24.15
unnamed: U22.20, U24.11
unnamed: U22.21, U23.4, U25.4
unnamed: U22.43, U24.8
unnamed: U22.44, U24.6
unnamed: U22.45, U24.4
unnamed: U22.46, U24.2
unnamed: U22.47, U23.5, U25.5
unnamed: U22.48, U23.16, U25.16
unnamed: U27.5, U29.3
unnamed: U27.9, U30.9, U63.9
unnamed: U28.14, Y2.2
unnamed: U31.2, U31.6
unnamed: U31.3, U31.4, U56.2
unnamed: U31.5, U56.6
unnamed: U31.12, U56.5
unnamed: U8.11, U32.26
unnamed: U8.3, U37.5
unnamed: U7.23, U54.6
unnamed: U54.8, U57.13
unnamed: U54.3, U54.10
unnamed: U7.22, U54.11
unnamed: U8.8, U58.1, U58.10
unnamed: U61.6, U61.9
POTX: C108.2, U2.2, U2.9, U5.24
POTY: C109.2, U2.3, U2.10, U5.23
R~W: CN1.5, RP1.2, U1.22, U4.22, U5.7, U7.32, U11.10, U21.14, U57.2
TOD: U1.19, U4.19, U16.6
VA6: U17.17, U21.38, U26.3
VA7: U17.18, U21.39, U26.6
VA14: RP1.7, U26.2, U63.10
VA15: RP1.8, U26.5, U63.12
Z80_R~W: U8.5, U13.1, U13.19, U31.11
~AEC: R40.2, U8.2, U14.15, U15.15, U29.10, U55.19
~BUSACK: U10.23, U37.11
~CAS: U9.10, U9.12, U11.47, U21.20
~CS_8563: U3.13, U22.7
~CS_CHAROM: U11.46, U18.20
~CS_CIA1: U1.23, U3.11
~CS_CIA2: U3.10, U4.23
~CS_COLRAM: U11.45, U19.18, U19.20
~CS_FROM: U11.33, U36.22
~CS_IO1: CN1.7, U3.9
~CS_IO2: CN1.10, U3.7
~CS_ROM1: U11.37, U32.22
~CS_ROM2: U11.36, U33.22
~CS_ROM3: U11.35, U34.22
~CS_ROM4: U11.34, U35.22
~CS_ROMH: CN1.B, U11.31
~CS_ROML: CN1.11, U11.30
~CS_SID: U3.15, U5.8
~CS_VIC: U11.42, U21.13
~DMA: CN1.13, R43.2, U55.1, U61.1, U61.12, U62.1, U62.19
~DRESET: CN7.7, RP2.8, U30.10
~DWE: U11.40, U38.3, U39.3, U40.3, U41.3, U42.3, U43.3, U44.3, U45.3, U46.3, U47.3, U48.3, U49.3, U50.3, U51.3, U52.3, U53.3
~EXROM: CN1.9, RP5.8, U7.46, U11.12
~FSDIR: U7.44, U16.13, U58.4, U58.13
~GAME: CN1.8, RP5.7, U7.45, U11.11
~GCAS0: U9.3, U9.9
~GCAS1: U9.6, U9.13
~GWE: U11.44, U56.12
~IOACC: U11.43, U21.22
~IRQ: CN1.4, R10.2, U1.21, U6.3, U10.16, U21.8
~LP: EMI32.3, EMI69.3, U1.14, U21.9, U22.25
~M1: U10.27, U31.10
~MMU_Z80EN: U7.43, U37.9, U61.5
~NMI: CN1.D, RP2.5, U4.21, U6.4, U29.4
~PLA_Z80EN: RP2.9, U8.1, U11.13, U37.10, U61.13
~RAS: R1.2, U21.19, U26.13
~RESET: CN1.C, RP2.7, U1.34, U4.34, U5.5, U6.40, U7.2, U10.26, U22.23, U57.11, U63.2, U63.3, U63.8
~VA14: U4.2, U11.26, U63.11
~Z80_IO: RP7.10, U10.20, U11.14
~ΦDOT: CN1.6, FB18.1
ΦCOLOR: U21.29, U28.8
ΦDOT: U21.30, U28.6, U29.1
ΦZ80: U21.25, U60.11, U60.13
